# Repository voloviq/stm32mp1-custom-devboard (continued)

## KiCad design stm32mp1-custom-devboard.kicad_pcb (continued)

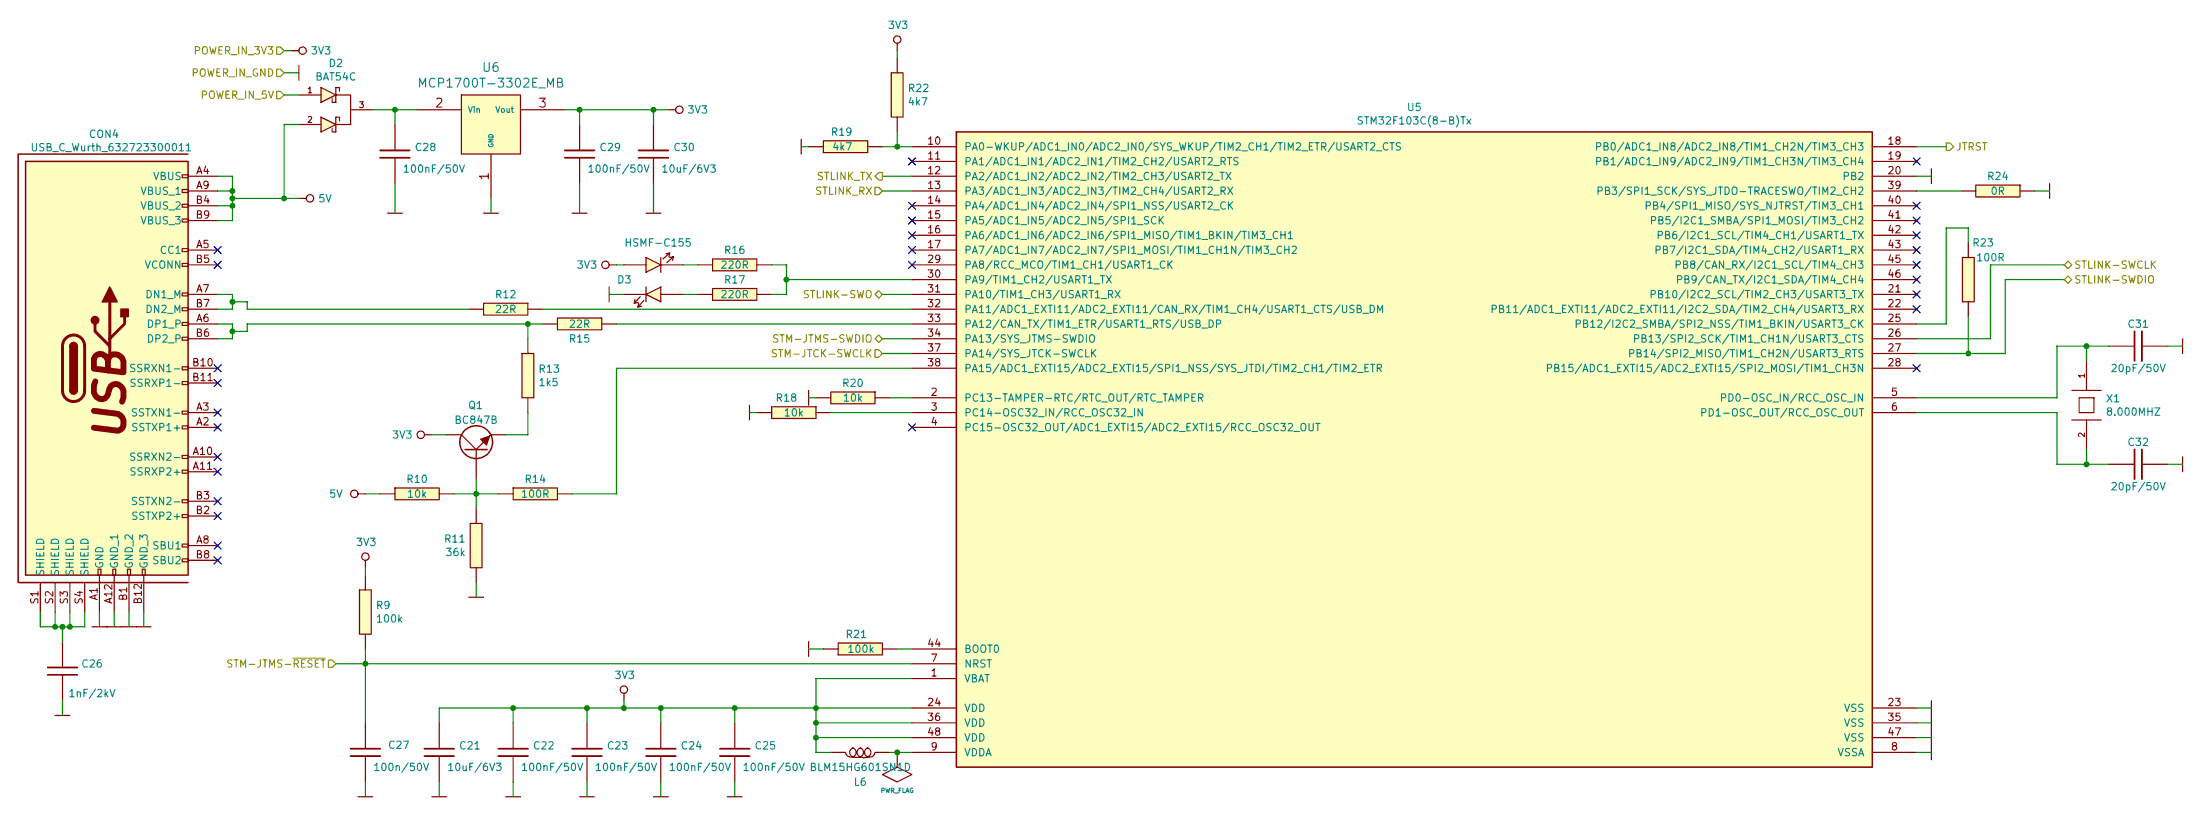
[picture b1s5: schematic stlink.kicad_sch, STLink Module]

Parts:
C21, C30: 10uF/6V3; 10uF_0805; Manufacturer Part Number CC0805KKX5R5BB106; LCSC Part # (optional) C386087
C22, C23, C24, C25, C28, C29: 100nF/50V; 100nF_0603; Manufacturer Part Number CL10B104JB8NNNC
C26: 1nF/2kV; 1nF_2kV_1206; Manufacturer Part Number CC1206KKX7RDBB102
C27: 100n/50V; 100nF_0603; Manufacturer Part Number CL10B104JB8NNNC
C31, C32: 20pF/50V; 20pF_0603; Manufacturer Part Number C0603C200J5GACTU; LCSC Part #(optional) C165733
CON4: USB_C_Wurth_632723300011; 632723300011; Manufacturer Part Number 632723300011
D2: BAT54C; Manufacturer Part Number BAT54C.215; LCSC Part #(optional) C369922
D3: HSMF-C155; Manufacturer Part Number HSMF-C155; LCSC Part #(optional) C188725
L6: BLM15HG601SN1D; BLM15HG601SN1D_0402
Q1: BC847B; BC847B_SOT23; Manufacturer Part Number BC847BE6327
R9, R21: 100k; 100k_0603; Manufacturer Part Number HP03W5J0104T5E; LCSC Part # (optional) C269699
R10, R18, R20: 10k; 10k_0603; Manufacturer Part Number 0603SAJ0103T5E
R11: 36k; 36k_0603; Manufacturer Part Number 0603SAJ0363T5E; LCSC Part #(optional) C170729
R12, R15: 22R; 22R_0603; Manufacturer Part Number CQ03SAF220JT5E; LCSC Part #(optional) C177623
R13: 1k5; 1k5_0603; Manufacturer Part Number 0603SAF1501T5E; LCSC Part # (optional) C177600
R14, R23: 100R; 100R_0603; Manufacturer Part Number CQ03SAF1000T5E; LCSC Part #(optional) C269700
R16, R17: 220R; 220R_0603; Manufacturer Part Number CQ03SAF2203T5E; LCSC Part #(optional) C103414
R19, R22: 4k7; 4k7_0603; Manufacturer Part Number 0603SAF4701T5E
R24: 0R; 0R_0603; Manufacturer Part Number 0603SAJ0000T5E; LCSC Part #(optional) C15402
U5: STM32F103C(8-B)Tx; STM32F103CBT6; Manufacturer Part Number STM32F103CBT6; LCSC Part #(optional) C8304
U6: MCP1700T-3302E_MB; MCP1700T-3302E_MB_SOT89; Manufacturer Part Number MCP1700T-3302E/MB
X1: 8.000MHZ; ABM3AIG-8.000MHZ-8-1R-T; Manufacturer Part Number ABM3AIG-8.000MHZ-8-1R-T

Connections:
3V3: C21.1, C22.1, C23.1, C24.1, C25.1, C29.1, C30.1, D3.1 (A1), L6.2, Q1.3 (C), R9.1, R22.1, U5.1 (VBAT), U5.24 (VDD), U5.36 (VDD), U5.48 (VDD), U6.3 (Vout); also elsewhere on the board
5V: CON4.A4 (VBUS), CON4.A9 (VBUS_1), CON4.B4 (VBUS_2), CON4.B9 (VBUS_3), D2.1 (A), D2.2 (A), R10.1; also elsewhere on the board
/STLink Module/JTRST: U5.18 (PB0/ADC1_IN8/ADC2_IN8/TIM1_CH2N/TIM3_CH3); also elsewhere on the board
/STLink Module/STLINK-SWCLK: U5.26 (PB13/SPI2_SCK/TIM1_CH1N/USART3_CTS); also elsewhere on the board
/STLink Module/STLINK-SWDIO: R23.1, U5.27 (PB14/SPI2_MISO/TIM1_CH2N/USART3_RTS); also elsewhere on the board
/STLink Module/STLINK-SWO: U5.31 (PA10/TIM1_CH3/USART1_RX); also elsewhere on the board
/STLink Module/STLINK_RX: U5.13 (PA3/ADC1_IN3/ADC2_IN3/TIM2_CH4/USART2_RX); also elsewhere on the board
/STLink Module/STLINK_TX: U5.12 (PA2/ADC1_IN2/ADC2_IN2/TIM2_CH3/USART2_TX); also elsewhere on the board
/STLink Module/STM-JTCK-SWCLK: U5.37 (PA14/SYS_JTCK-SWCLK); also elsewhere on the board
/STLink Module/STM-JTMS-SWDIO: U5.34 (PA13/SYS_JTMS-SWDIO); also elsewhere on the board
/STLink Module/STM-JTMS-~RESET: C27.1, R9.2, U5.7 (NRST); also elsewhere on the board
GND: C21.2, C22.2, C23.2, C24.2, C25.2, C26.1, C27.2, C28.2, C29.2, C30.2, C31.1, C32.1, CON4.A1 (GND), CON4.A12 (GND_1), CON4.B1 (GND_2), CON4.B12 (GND_3), D3.4 (C2), R11.1, R18.2, R19.1, R20.2, R21.1, R24.1, U5.8 (VSSA), U5.20 (PB2), U5.23 (VSS), U5.35 (VSS), U5.47 (VSS), U6.1 (GND); also elsewhere on the board
unnamed: C26.2, CON4.S1 (SHIELD), CON4.S2 (SHIELD), CON4.S3 (SHIELD), CON4.S4 (SHIELD)
unnamed: C28.1, D2.3 (K), U6.2 (Vin)
unnamed: C31.2, U5.5 (PD0-OSC_IN/RCC_OSC_IN), X1.1
unnamed: C32.2, U5.6 (PD1-OSC_OUT/RCC_OSC_OUT), X1.2
unnamed: CON4.A6 (DP1_P), CON4.B6 (DP2_P), R13.1, R15.2
unnamed: CON4.A7 (DN1_M), CON4.B7 (DN2_M), R12.2
unnamed: D3.2 (C1), R16.1
unnamed: D3.3 (A2), R17.1
unnamed: L6.1, U5.9 (VDDA)
unnamed: Q1.1 (B), R10.2, R11.2, R14.1
unnamed: Q1.2 (E), R13.2
unnamed: R12.1, U5.32 (PA11/ADC1_EXTI11/ADC2_EXTI11/CAN_RX/TIM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)
unnamed: R14.2, U5.38 (PA15/ADC1_EXTI15/ADC2_EXTI15/SPI1_NSS/S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)
unnamed: R15.1, U5.33 (PA12/CAN_TX/TIM1_ETR/USART1_RTS/USB_DP)
unnamed: R16.2, R17.2, U5.30 (PA9/TIM1_CH2/USART1_TX)
unnamed: R18.1, U5.3 (PC14-OSC32_IN/RCC_OSC32_IN)
unnamed: R19.2, R22.2, U5.10 (PA0-WKUP/ADC1_IN0/ADC2_IN0/SYS_WKUP/TIM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)
unnamed: R20.1, U5.2 (PC13-TAMPER-RTC/RTC_OUT/RTC_TAMPER)
unnamed: R21.2, U5.44 (BOOT0)
unnamed: R23.2, U5.25 (PB12/I2C2_SMBA/SPI2_NSS/TIM1_BKIN/USART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)
unnamed: R24.2, U5.39 (PB3/SPI1_SCK/SYS_JTDO-TRACESWO/TIM2_CH2)

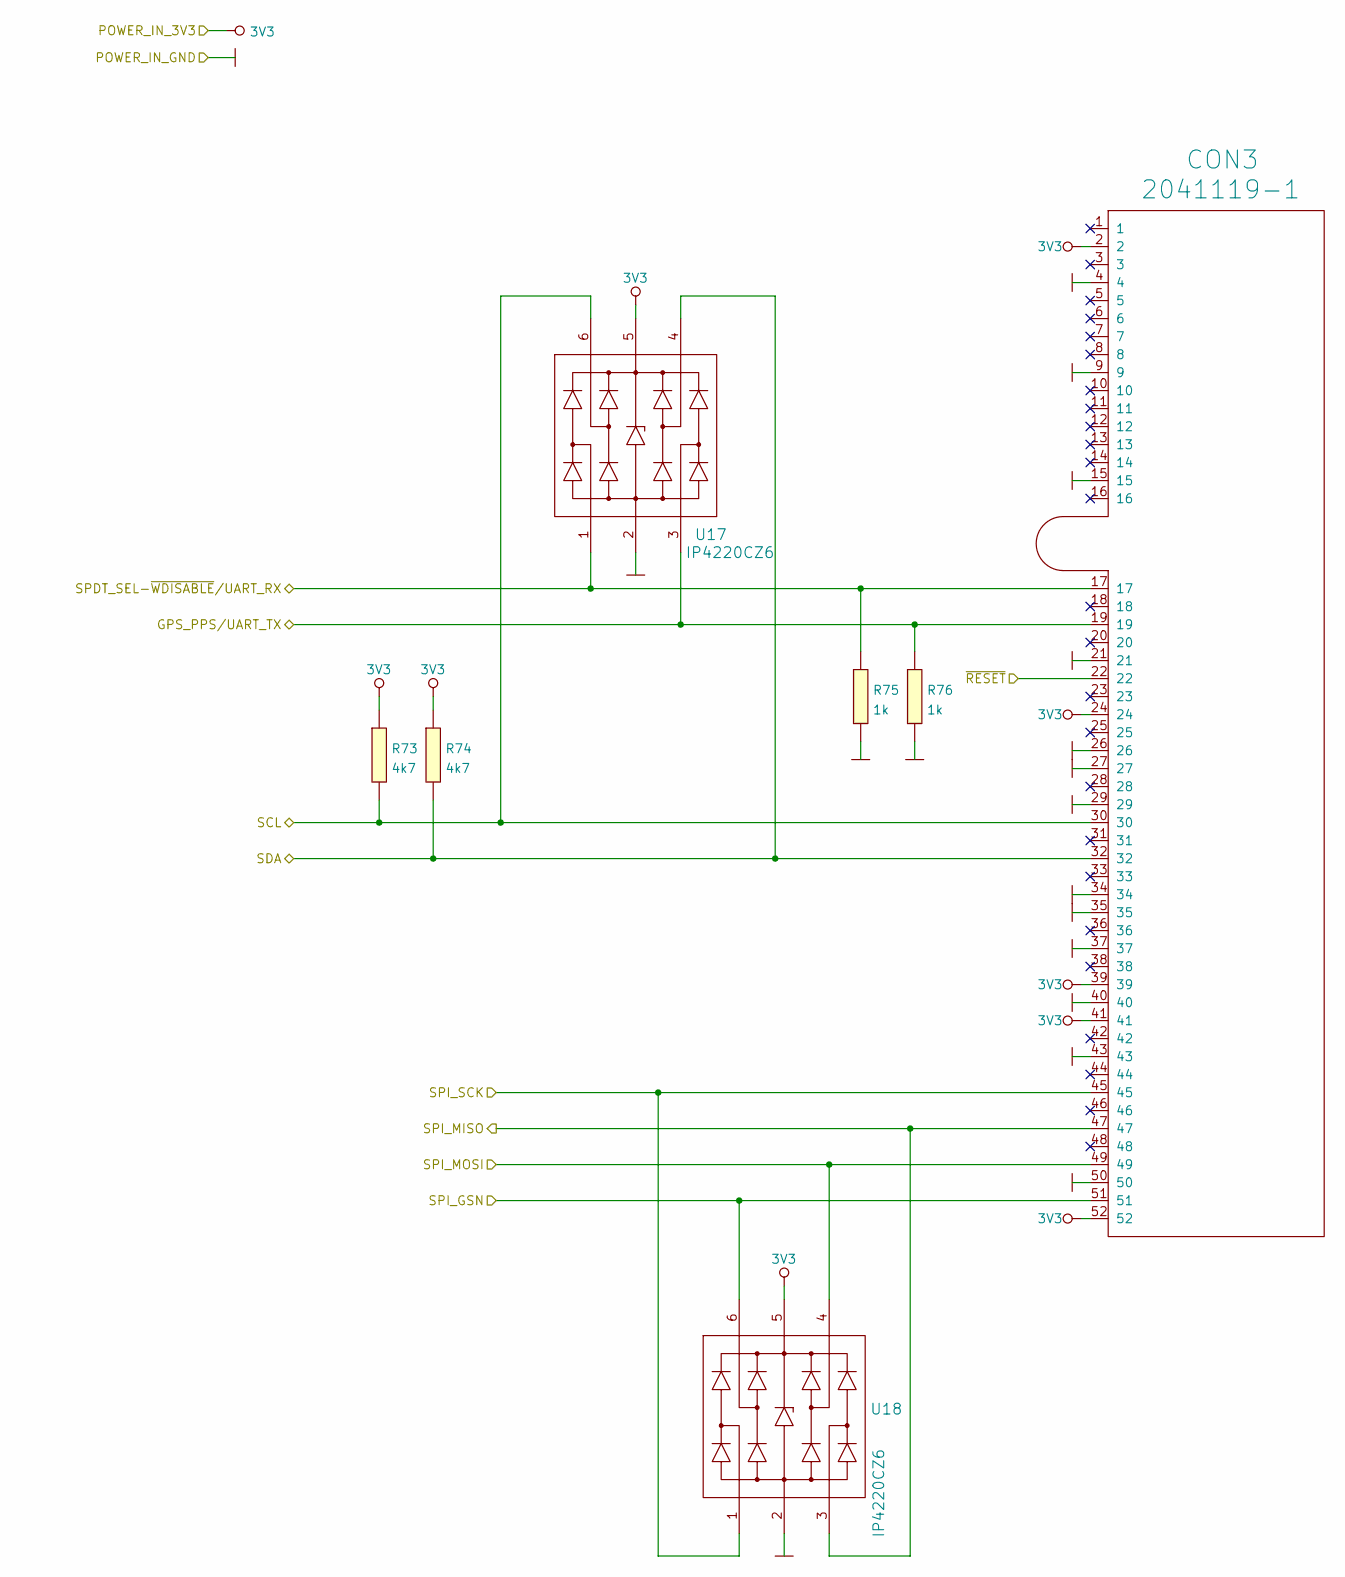
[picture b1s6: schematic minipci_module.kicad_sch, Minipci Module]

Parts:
CON3: 2041119-1; Manufacturer Part Number 2041119-1
R73, R74: 4k7; 4k7_0402; Manufacturer Part Number 0402WGF4701TCE
R75, R76: 1k; 1k_0402; Manufacturer Part Number SMD0402-1K-1%; LCSC Part #(optional) C269675
U17, U18: IP4220CZ6; IP4220CZ6_SOT457; Manufacturer Part Number IP4220CZ6.125; LCSC Part #(optional) C2687127

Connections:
3V3: CON3.2, CON3.24, CON3.39, CON3.41, CON3.52, R73.1, R74.1, U17.5 (Vp), U18.5 (Vp); also elsewhere on the board
/MiniPci Module/GPS_PPS/UART_TX: CON3.19, R76.1, U17.3 (I/O2); also elsewhere on the board
/MiniPci Module/SCL: CON3.30, R73.2, U17.6 (I/O4); also elsewhere on the board
/MiniPci Module/SDA: CON3.32, R74.2, U17.4 (I/O3); also elsewhere on the board
/MiniPci Module/SPDT_SEL-~WDISABLE/UART_RX: CON3.17, R75.1, U17.1 (I/O1); also elsewhere on the board
/MiniPci Module/SPI_GSN: CON3.51, U18.6 (I/O4); also elsewhere on the board
/MiniPci Module/SPI_MISO: CON3.47, U18.3 (I/O2); also elsewhere on the board
/MiniPci Module/SPI_MOSI: CON3.49, U18.4 (I/O3); also elsewhere on the board
/MiniPci Module/SPI_SCK: CON3.45, U18.1 (I/O1); also elsewhere on the board
/MiniPci Module/~RESET: CON3.22; also elsewhere on the board
GND: CON3.4, CON3.9, CON3.15, CON3.21, CON3.26, CON3.27, CON3.29, CON3.34, CON3.35, CON3.37, CON3.40, CON3.43, CON3.50, R75.2, R76.2, U17.2 (GND), U18.2 (GND); also elsewhere on the board

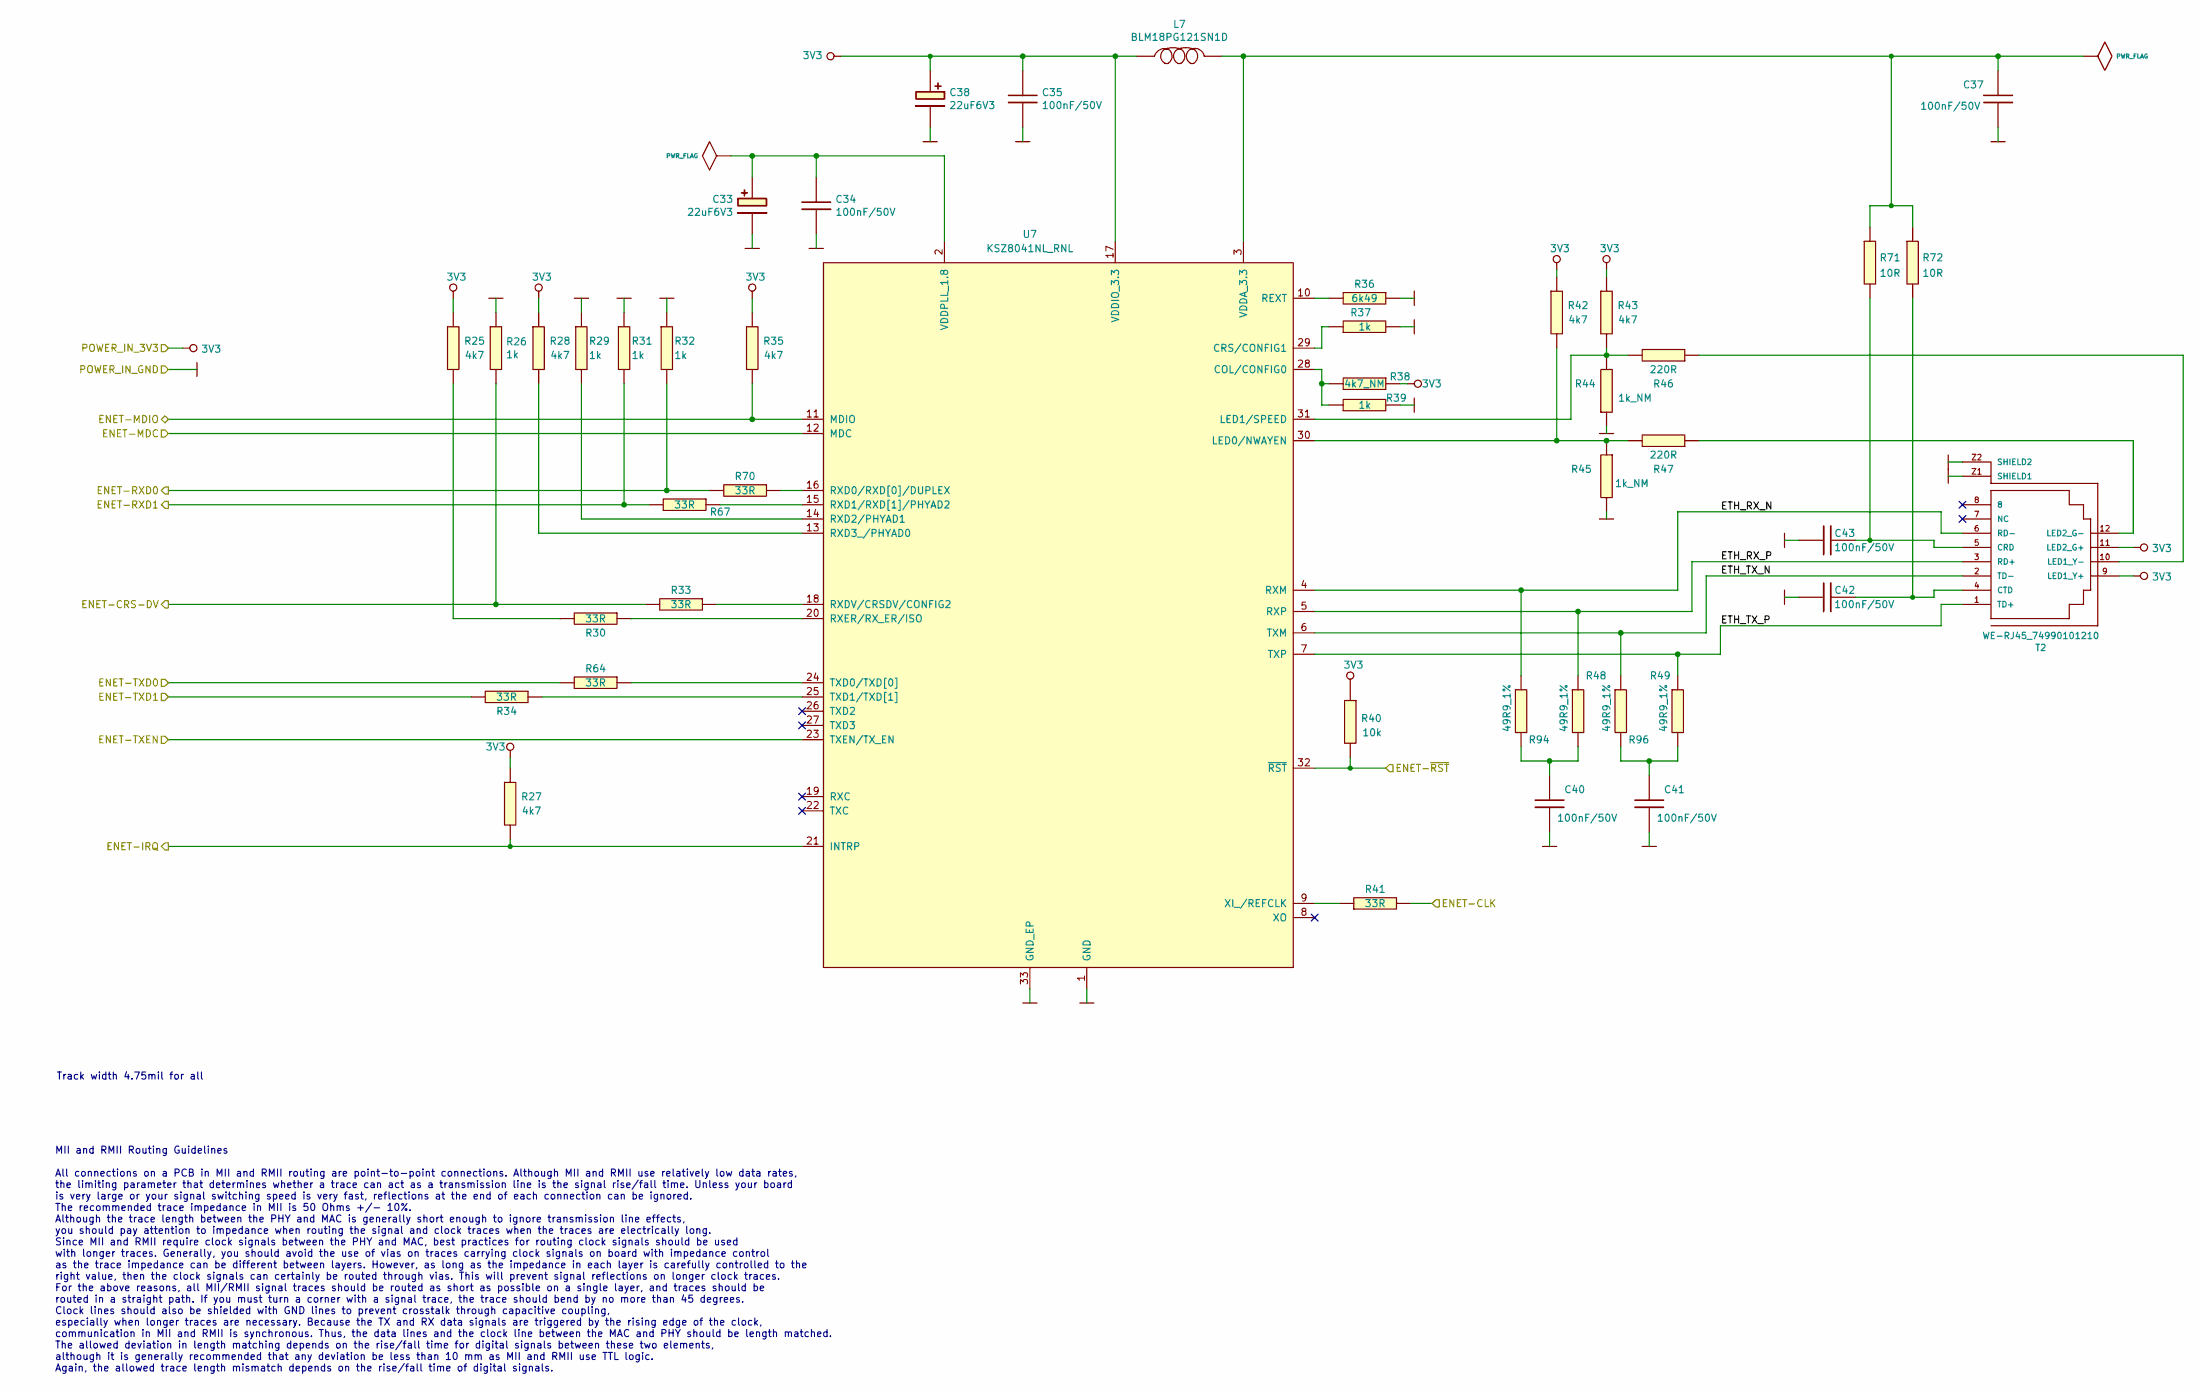
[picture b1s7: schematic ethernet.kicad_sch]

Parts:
C33, C38: 22uF6V3; 22uF6V3_1206; Manufacturer Part Number 293D226X9010C2TE3; LCSC Part #(optional) C123266
C34, C35, C37, C40, C41, C42, C43: 100nF/50V; 100nF_0402; Manufacturer Part Number CL10B104JB8NNNC; LCSC Part # (optional) C131394
L7: BLM18PG121SN1D; BLM18PG121SN1D_SM0603
R25, R27, R28, R35, R42, R43: 4k7; 4k7_0603
R26, R29, R31, R32, R37, R39: 1k; 1k_0603
R30, R33, R34, R41, R64, R67, R70: 33R; 33R_0402; Manufacturer Part Number CQ02WGF330JTCE; LCSC Part #(optional) C208868
R36: 6k49; 6k49_0603
R38: 4k7_NM; 4k7_0603
R40: 10k; 10k_0603
R44, R45: 1k_NM; 1k_0603
R46, R47: 220R; 220R_0603
R48, R49, R94, R96: 49R9_1%; 49R9_0402; Manufacturer Part Number 0402WGF499JTCE; LCSC Part #(optional) C325388
R71, R72: 10R; 10R_0402; Manufacturer Part Number 0402WGF100JTCE; LCSC Part # (optional) C269385
T2: WE-RJ45_74990101210; Manufacturer Part Number 74990101210
U7: KSZ8041NL_RNL; KSZ8041NL_RNL_QFN32; Manufacturer Part Number KSZ8041NL-TR; LCSC Part #(optional) C11146

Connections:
3V3: C35.1, C38.1, L7.1, R25.1, R27.1, R28.1, R35.1, R38.1, R40.1, R42.1, R43.1, T2.9 (LED1_Y+), T2.11 (LED2_G+), U7.17 (VDDIO_3.3); also elsewhere on the board
/Ethernet Module/ENET-CLK: R41.2; also elsewhere on the board
/Ethernet Module/ENET-CRS-DV: R26.2, R33.2; also elsewhere on the board
/Ethernet Module/ENET-IRQ: R27.2, U7.21 (INTRP); also elsewhere on the board
/Ethernet Module/ENET-MDC: U7.12 (MDC); also elsewhere on the board
/Ethernet Module/ENET-MDIO: R35.2, U7.11 (MDIO); also elsewhere on the board
/Ethernet Module/ENET-RXD0: R32.2, R70.2; also elsewhere on the board
/Ethernet Module/ENET-RXD1: R31.2, R67.2; also elsewhere on the board
/Ethernet Module/ENET-TXD0: R64.2; also elsewhere on the board
/Ethernet Module/ENET-TXD1: R34.2; also elsewhere on the board
/Ethernet Module/ENET-TXEN: U7.23 (TXEN/TX_EN); also elsewhere on the board
/Ethernet Module/ENET-~RST: R40.2, U7.32 (~RST); also elsewhere on the board
/Ethernet Module/ETH_RX_N: R94.1, T2.6 (RD-), U7.4 (RXM)
/Ethernet Module/ETH_RX_P: R48.1, T2.3 (RD+), U7.5 (RXP)
/Ethernet Module/ETH_TX_N: R96.1, T2.2 (TD-), U7.6 (TXM)
/Ethernet Module/ETH_TX_P: R49.1, T2.1 (TD+), U7.7 (TXP)
GND: C33.2, C34.2, C35.2, C37.2, C38.2, C40.2, C41.2, C42.1, C43.1, R26.1, R29.1, R31.1, R32.1, R36.1, R37.2, R39.2, R44.1, R45.2, T2.Z1 (SHIELD1), T2.Z2 (SHIELD2), U7.1 (GND), U7.33 (GND_EP); also elsewhere on the board
unnamed: C33.1, C34.1, U7.2 (VDDPLL_1.8)
unnamed: C37.1, L7.2, R71.1, R72.1, U7.3 (VDDA_3.3)
unnamed: C40.1, R48.2, R94.2
unnamed: C41.1, R49.2, R96.2
unnamed: C42.2, R72.2, T2.4 (CTD)
unnamed: C43.2, R71.2, T2.5 (CRD)
unnamed: R25.2, R30.2
unnamed: R28.2, U7.13 (RXD3_/PHYAD0)
unnamed: R29.2, U7.14 (RXD2/PHYAD1)
unnamed: R30.1, U7.20 (RXER/RX_ER/ISO)
unnamed: R33.1, U7.18 (RXDV/CRSDV/CONFIG2)
unnamed: R34.1, U7.25 (TXD1/TXD[1])
unnamed: R36.2, U7.10 (REXT)
unnamed: R37.1, U7.29 (CRS/CONFIG1)
unnamed: R38.2, R39.1, U7.28 (COL/CONFIG0)
unnamed: R41.1, U7.9 (XI_/REFCLK)
unnamed: R42.2, R45.1, R47.2, U7.30 (LED0/NWAYEN)
unnamed: R43.2, R44.2, R46.2, U7.31 (LED1/SPEED)
unnamed: R46.1, T2.10 (LED1_Y-)
unnamed: R47.1, T2.12 (LED2_G-)
unnamed: R64.1, U7.24 (TXD0/TXD[0])
unnamed: R67.1, U7.15 (RXD1/RXD[1]/PHYAD2)
unnamed: R70.1, U7.16 (RXD0/RXD[0]/DUPLEX)

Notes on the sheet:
Track width 4.75mil for all
MII and RMII Routing Guidelines All connections on a PCB in MII and RMII routing are point-to-point connections. Although MII and RMII use relatively low data rates, the limiting parameter that determines whether a trace can act as a transmission line is the signal rise/fall time. Unless your board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

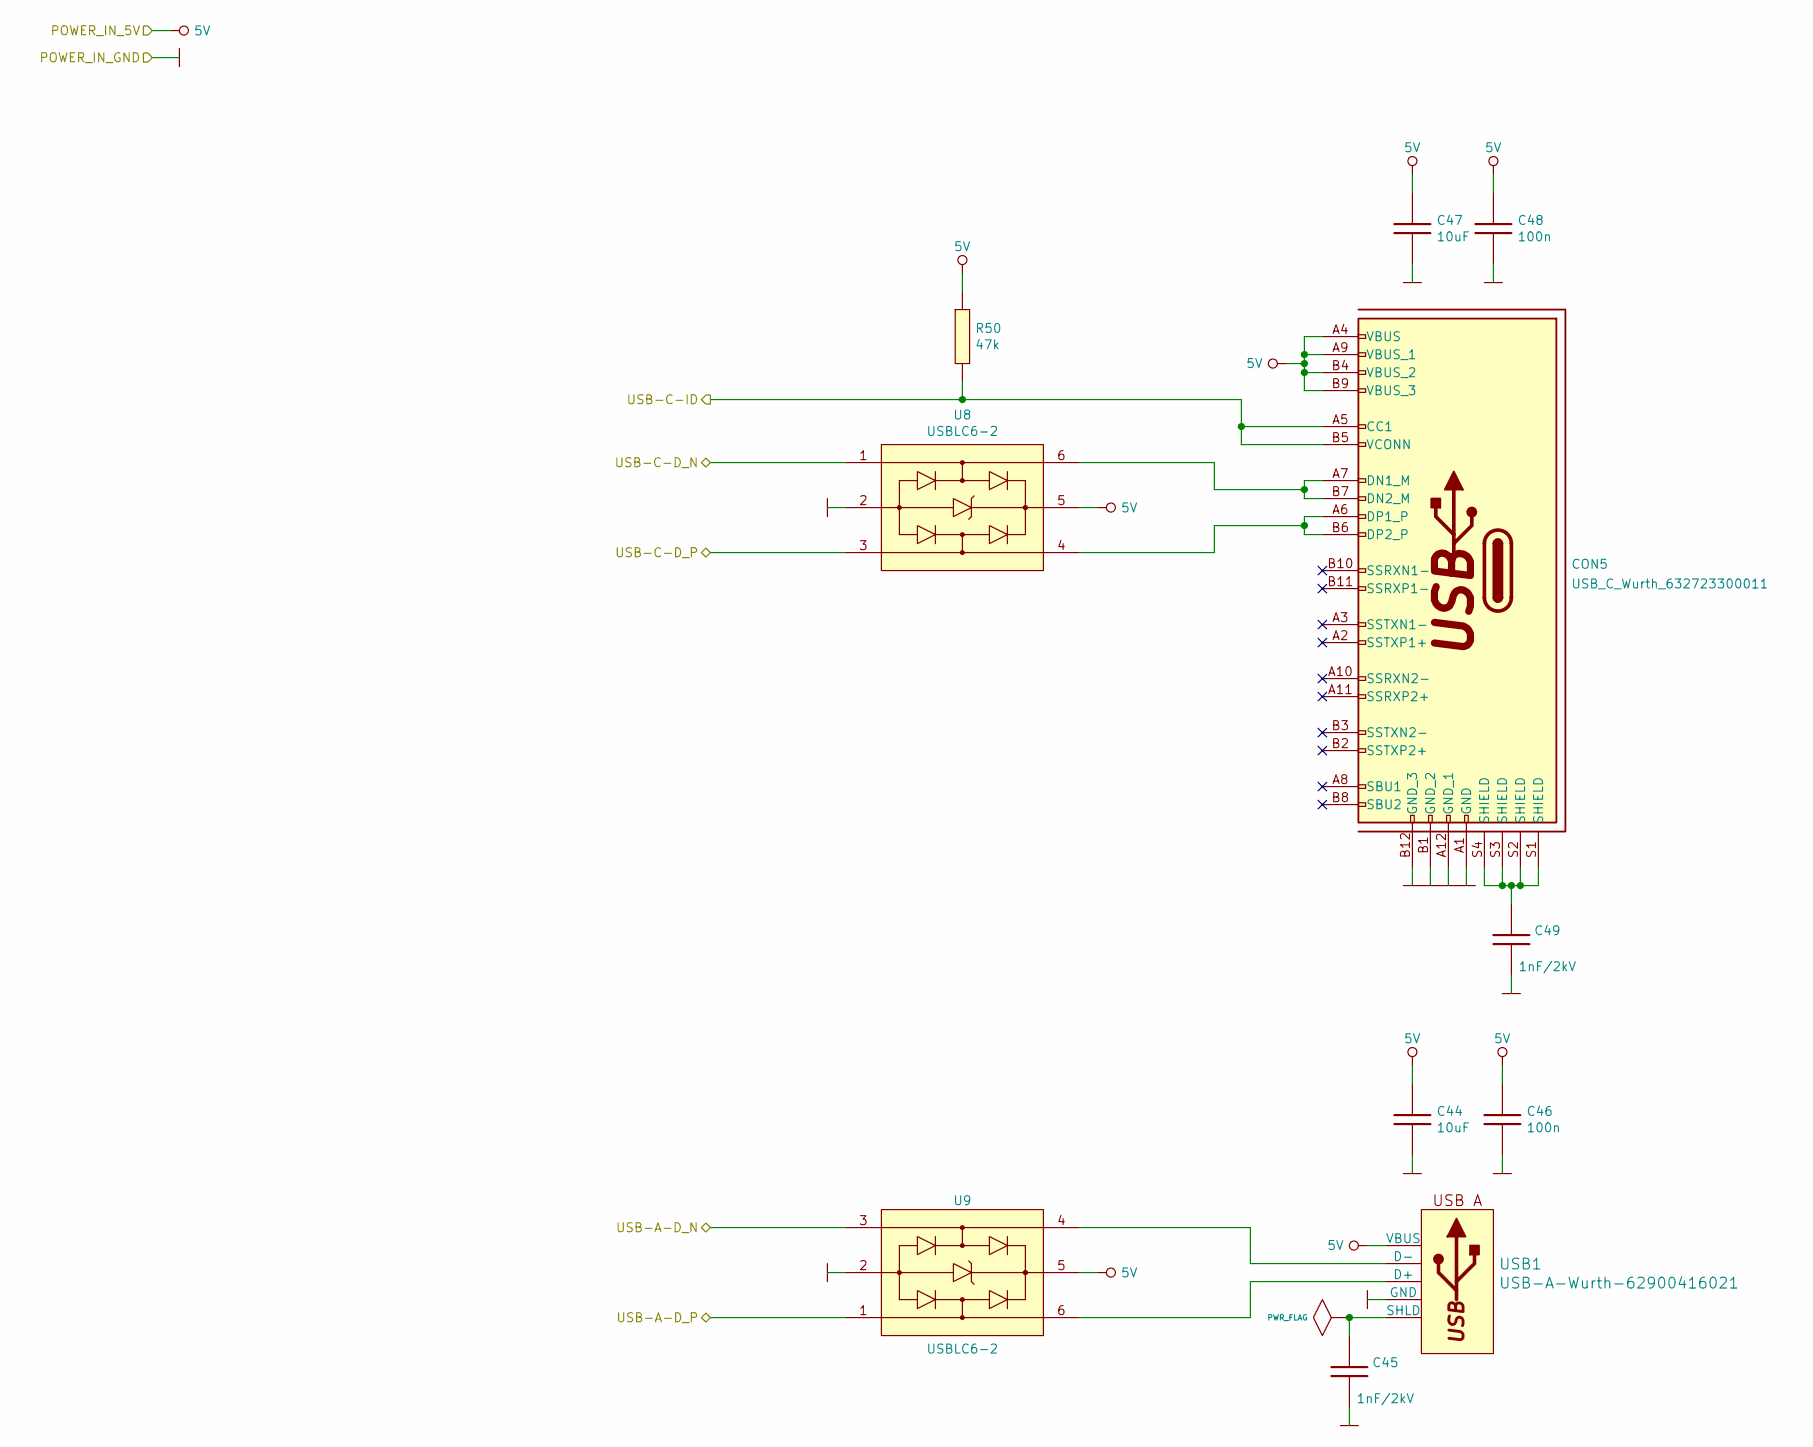
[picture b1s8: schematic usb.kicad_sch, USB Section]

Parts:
C44, C47: 10uF; 10uF_10V_0603; Manufacturer Part Number C0603C106M9PACTU; LCSC Part # (optional) C162265
C45, C49: 1nF/2kV; 1nF_2kV_1206; Manufacturer Part Number CC1206KKX7RDBB102
C46, C48: 100n; 100nF_0603; Manufacturer Part Number CL10B104JB8NNNC
CON5: USB_C_Wurth_632723300011; 632723300011; Manufacturer Part Number 632723300011
R50: 47k; 47k_0603; Manufacturer Part Number 0603SAF4702T5E; LCSC Part #(optional) C105579
U8, U9: USBLC6-2; USBLC6-2_SOT23-6L; Manufacturer Part Number USBLC6-2SC6; LCSC Part #(optional) C7519
USB1: USB-A-Wurth-62900416021; Wurth-62900416021; Manufacturer Part Number 62900416021

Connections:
5V: C44.1, C46.1, C47.1, C48.1, CON5.A4 (VBUS), CON5.A9 (VBUS_1), CON5.B4 (VBUS_2), CON5.B9 (VBUS_3), R50.1, U8.5, U9.5, USB1.1 (VBUS); also elsewhere on the board
/STM32MP1 module/PA13-GPIO: CON5.A5 (CC1), CON5.B5 (VCONN), R50.2; also elsewhere on the board
/STM32MP1 module/USB-OTG1-D_N: U9.3; also elsewhere on the board
/STM32MP1 module/USB-OTG1-D_P: U9.1; also elsewhere on the board
/STM32MP1 module/USB-OTG2-D_N: U8.1; also elsewhere on the board
/STM32MP1 module/USB-OTG2-D_P: U8.3; also elsewhere on the board
GND: C44.2, C45.1, C46.2, C47.2, C48.2, C49.1, CON5.A1 (GND), CON5.A12 (GND_1), CON5.B1 (GND_2), CON5.B12 (GND_3), U8.2, U9.2, USB1.4 (GND); also elsewhere on the board
unnamed: C45.2, USB1.SH (SHLD)
unnamed: C49.2, CON5.S1 (SHIELD), CON5.S2 (SHIELD), CON5.S3 (SHIELD), CON5.S4 (SHIELD)
unnamed: CON5.A6 (DP1_P), CON5.B6 (DP2_P), U8.4
unnamed: CON5.A7 (DN1_M), CON5.B7 (DN2_M), U8.6
unnamed: U9.4, USB1.2 (D-)
unnamed: U9.6, USB1.3 (D+)

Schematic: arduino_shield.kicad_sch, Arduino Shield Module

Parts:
C50, C51: 10uF; 10uF_10V_0603; Manufacturer Part Number C0603C106M9PACTU; LCSC Part # (optional) C162265
C52, C53: 100n; 100nF_0603; Manufacturer Part Number CL10B104JB8NNNC
R60, R61: 4k7; 4k7_0603; Manufacturer Part Number 0603SAF4701T5E
U12, U13, U14, U15, U16: IP4220CZ6; IP4220CZ6_SOT457; Manufacturer Part Number IP4220CZ6.125; LCSC Part #(optional) C2687127
XA1: Arduino_101_Shield

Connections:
3V3: C51.1, C53.1, R60.1, R61.1, U12.5 (Vp), U13.5 (Vp), U14.5 (Vp), U15.5 (Vp), U16.5 (Vp), XA1.3V3 (3.3V); also elsewhere on the board
5V: C50.1, C52.1, XA1.5V1 (5V), XA1.5V2 (SPI_5V); also elsewhere on the board
/Arduino Shield Module/ANALOG_A0: XA1.A0; also elsewhere on the board
/Arduino Shield Module/ANALOG_A1: XA1.A1; also elsewhere on the board
/Arduino Shield Module/ANALOG_A2: XA1.A2; also elsewhere on the board
/Arduino Shield Module/ANALOG_A3: XA1.A3; also elsewhere on the board
/Arduino Shield Module/ANALOG_A4: XA1.A4; also elsewhere on the board
/Arduino Shield Module/ANALOG_A5: XA1.A5; also elsewhere on the board
/Arduino Shield Module/ATN: XA1.ATN; also elsewhere on the board
/Arduino Shield Module/GPIO-D2: U13.1 (I/O1), XA1.D2; also elsewhere on the board
/Arduino Shield Module/GPIO-D3: U13.3 (I/O2), XA1.D3; also elsewhere on the board
/Arduino Shield Module/GPIO-D4: U13.6 (I/O4), XA1.D4; also elsewhere on the board
/Arduino Shield Module/GPIO-D5: U13.4 (I/O3), XA1.D5; also elsewhere on the board
/Arduino Shield Module/GPIO-D6: U14.1 (I/O1), XA1.D6; also elsewhere on the board
/Arduino Shield Module/GPIO-D7: U14.3 (I/O2), XA1.D7; also elsewhere on the board
/Arduino Shield Module/GPIO-D8: U14.6 (I/O4), XA1.D8; also elsewhere on the board
/Arduino Shield Module/GPIO-D9: U14.4 (I/O3), XA1.D9; also elsewhere on the board
/Arduino Shield Module/GPIO-D10: U16.1 (I/O1), XA1.D10 (D10_CS); also elsewhere on the board
/Arduino Shield Module/GPIO-D11: U16.3 (I/O2), XA1.D11; also elsewhere on the board
/Arduino Shield Module/GPIO-D12: U16.6 (I/O4), XA1.D12; also elsewhere on the board
/Arduino Shield Module/GPIO-D13: U16.4 (I/O3), XA1.D13; also elsewhere on the board
/Arduino Shield Module/I2C-SCL: R60.2, U12.6 (I/O4), XA1.SCL; also elsewhere on the board
/Arduino Shield Module/I2C-SDA: R61.2, U12.4 (I/O3), XA1.SDA; also elsewhere on the board
/Arduino Shield Module/IOREF: XA1.IORF (IOREF); also elsewhere on the board
/Arduino Shield Module/RESET: XA1.RST1 (RESET); also elsewhere on the board
/Arduino Shield Module/SPI-MISO: U15.1 (I/O1), XA1.MISO (SPI_MISO); also elsewhere on the board
/Arduino Shield Module/SPI-MOSI: U15.3 (I/O2), XA1.MOSI (SPI_MOSI); also elsewhere on the board
/Arduino Shield Module/SPI-RST: U15.6 (I/O4), XA1.RST2 (SPI_RESET); also elsewhere on the board
/Arduino Shield Module/SPI-SCK: U15.4 (I/O3), XA1.SCK (SPI_SCK); also elsewhere on the board
/Arduino Shield Module/UART-RX0: U12.3 (I/O2), XA1.D0 (D0_RX0); also elsewhere on the board
/Arduino Shield Module/UART-TX0: U12.1 (I/O1), XA1.D1 (D1_TX0); also elsewhere on the board
GND: C50.2, C51.2, C52.2, C53.2, U12.2 (GND), U13.2 (GND), U14.2 (GND), U15.2 (GND), U16.2 (GND), XA1.GND1 (GND), XA1.GND2 (GND), XA1.GND3 (GND), XA1.GND4 (SPI_GND); also elsewhere on the board
VCC-RTC: XA1.AREF
VPP: XA1.VIN; also elsewhere on the board

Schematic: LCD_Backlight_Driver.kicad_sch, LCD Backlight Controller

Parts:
C1: 1uF/6V3; 1uF_0603; Manufacturer Part Number CL10B105KO8NNNC
C2: 4.7uF/35V; 4_7uF_0603; Manufacturer Part Number CL10A475KQ8NNNC
D1: NSR0530H-D; NSR0530H-D_SOD323
L3: 4.7uH-0.9A-74438333047; Manufacturer Part Number 74438333047
R1: 10Ω/1%/0.1Wat; 10R_0603; Manufacturer Part Number 0603SAF100JT5E; LCSC Part # (optional) C269702
U1: TPS61169DCKR; Manufacturer Part Number TPS61169DCKR; LCSC Part # (optional) C71045

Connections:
3V3: C1.1, L3.1, U1.5 (VIN); also elsewhere on the board
/LCD+Touchscreen/LCD Backlight Controller/BACKLIGHT_HIGH: C2.1, D1.1 (K); also elsewhere on the board
/LCD+Touchscreen/LCD Backlight Controller/BACKLIGHT_LOW: R1.1, U1.3 (FB); also elsewhere on the board
/LCD+Touchscreen/LCD_BACKLIGHT_PWM: U1.4 (CTRL); also elsewhere on the board
GND: C1.2, C2.2, R1.2, U1.2 (GND); also elsewhere on the board
unnamed: D1.2 (A), L3.2, U1.1 (SW)

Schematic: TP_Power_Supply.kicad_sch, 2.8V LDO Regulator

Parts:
C3, C4: 1uF/16V; 1uF_0603; Manufacturer Part Number CL10B105KO8NNNC
U2: MCP1703T-3302E; MCP1703T-3302E_SOT23; Manufacturer Part Number MCP1703T-3302E/CB; LCSC Part #(optional) C39051

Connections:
3V3: C3.1, U2.3 (Vin); also elsewhere on the board
/LCD+Touchscreen/Touchscreen Power Supply/VOUT_3.3V_250mA: C4.1, U2.2 (Vout); also elsewhere on the board
GND: C3.2, C4.2, U2.1 (GND); also elsewhere on the board

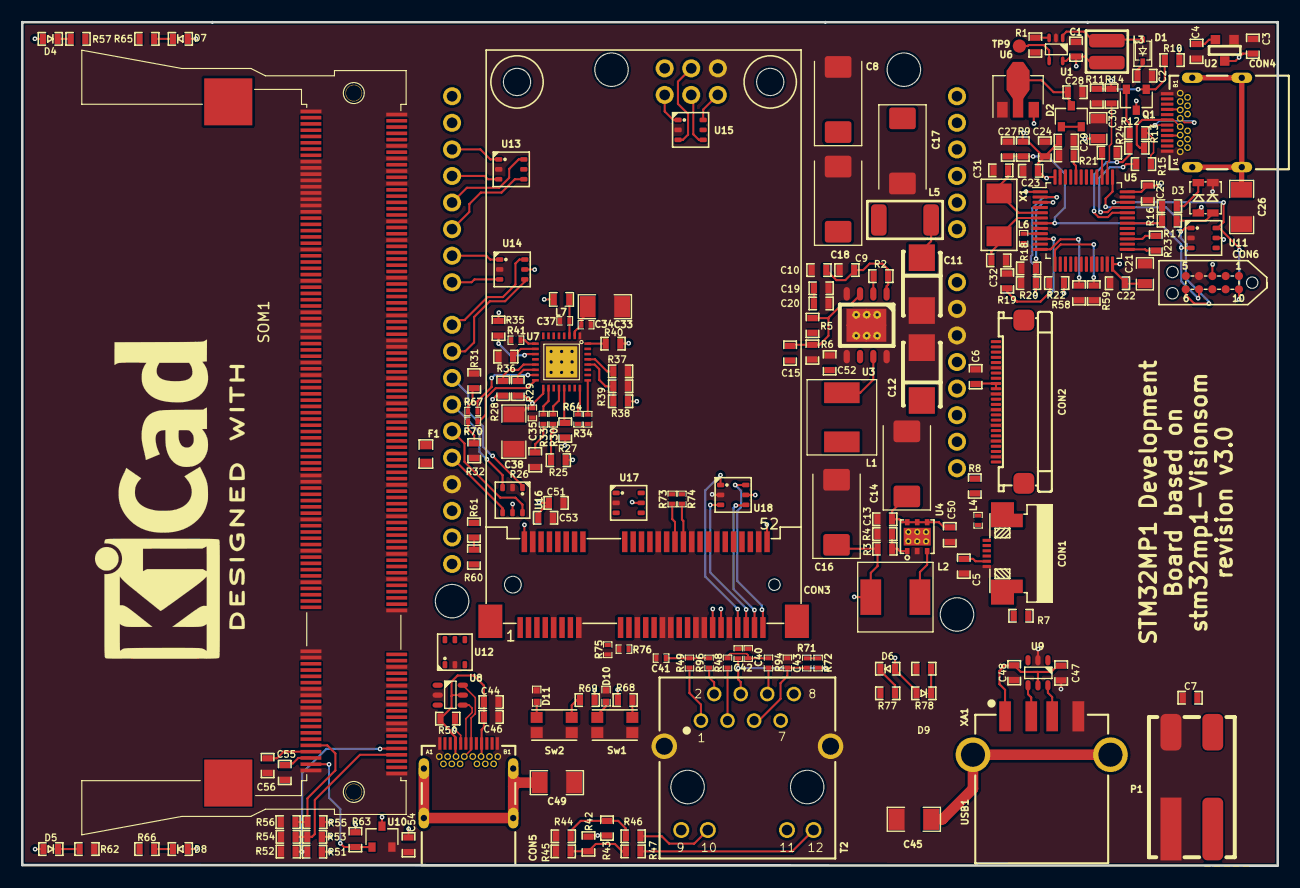
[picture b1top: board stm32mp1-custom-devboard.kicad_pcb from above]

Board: 4 copper layers, 120.0 x 80.6 mm, 194 parts (0 on the bottom side), 167 nets.

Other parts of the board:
REF1: KiCad-Logo2_12mm_SilkScreen

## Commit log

2020-12-19 Added display section
2020-12-19 Added stm32mp1 module and arduino shield
2020-12-19 Added new components and hierarchical sheets
2020-12-20 Added power source module
2020-12-20 Added Mipi Dsi connection, started stlink module
2021-01-10 Added minipci connector
2021-01-12 Continue work at jtag
2021-01-12 Finished work at st-link, figurated elements on pcb
2021-01-13 Added ethernet and usb module
2021-01-13 Added new USB connectors on schematic, figurated elements on pcb
2021-01-18 Updated schematic, added some components, figurated components on pcb
2021-01-18 Schematic work contiune, added pinout spreadsheet
2021-01-18 Schematic finished, elements figurated on pcb, tracking started
2021-01-19 Tracking in progress
2021-01-19 Tracking almost finished
2021-01-19 Tracking finished, started tunning
2021-01-20 Added gnd in stm32f swd interface
2021-01-20 Added missing components like LED diodes, i2c pull-up resistors
2021-01-20 Added BOM list
2021-01-20 BOM corrections
2021-01-20 Added missing URLs in BOM
2021-01-20 High speed track tuned, aligned BOM with JLCPCB option and position file, regenrated all production files
2021-01-23 Updated edge cut layer as JLCPCB suggest
2021-02-09 Updated BOM
2021-02-13 Stored current in new branch v1.0
2021-02-13 Started apply issues
2021-02-23 Issue 5 applied
2021-02-23 Applied issue 4
2021-02-25 Started issues implementation
2021-03-11 Tracking finished
2021-03-16 Reworked schematic and applied changes on pcb related with mini pci express
2021-03-16 Finalize project
2021-04-19 Updated schematic and pdf
2021-04-19 Added CubeMx configuration folder
2021-04-27 Generated schematic in pdf
2021-04-29 Modified ethernet
2021-04-29 Started etherner reworking
2021-05-11 Changed supply of 3.3V DC-DC converter
2021-05-12 Make all connections, started track tunning
2021-05-12 Added some rules for ethernet
2021-05-13 Rebuild all ethernet tracks to keep constant impedance
2021-05-22 Aligned USB C connectors on schematic and on pcb
2021-05-22 Ethernet tracking in progress
2021-05-23 Ethernet TXDx and RXDx tunned
2021-05-23 Almost all ethernet signals aligned
2021-05-24 Applied all changes, tunnign started
2021-05-24 Finalized project, regenerated gerbers
2021-05-25 Finalized project
2021-06-20 Updated schematic
2021-12-14 GAdded new branch v3.0
2021-12-17 Corrected schematic
2022-01-08 Rebuild board
2022-01-08 Placed all elements on pcb
2022-01-08 Updated 3d picture in README.md
2022-01-08 Updated place of capacitor
2022-01-08 Replaced some elements on pcb
2022-01-09 Removed unnecessary backup files
2022-01-15 Tracking finished, tunning started
2022-01-15 Cleared all errors DRC
2022-01-15 Eliminated all warnings realted with footprints
2022-01-15 Gerbers created, BOM, CPL
2022-01-15 Aligned BOM with JLCPCB
2022-01-16 Corrected 3.3V DC power path and regenerated gerbers
2022-04-07 New branch created
2022-04-08 Finalized
2022-04-08 Changed ethernet connector to horizontal and changed it position to avoid collision with arduino shield
2022-04-14 Added Housing Kradex Z113
2022-04-14 Removed unnecessary files
2022-04-27 Added new package
